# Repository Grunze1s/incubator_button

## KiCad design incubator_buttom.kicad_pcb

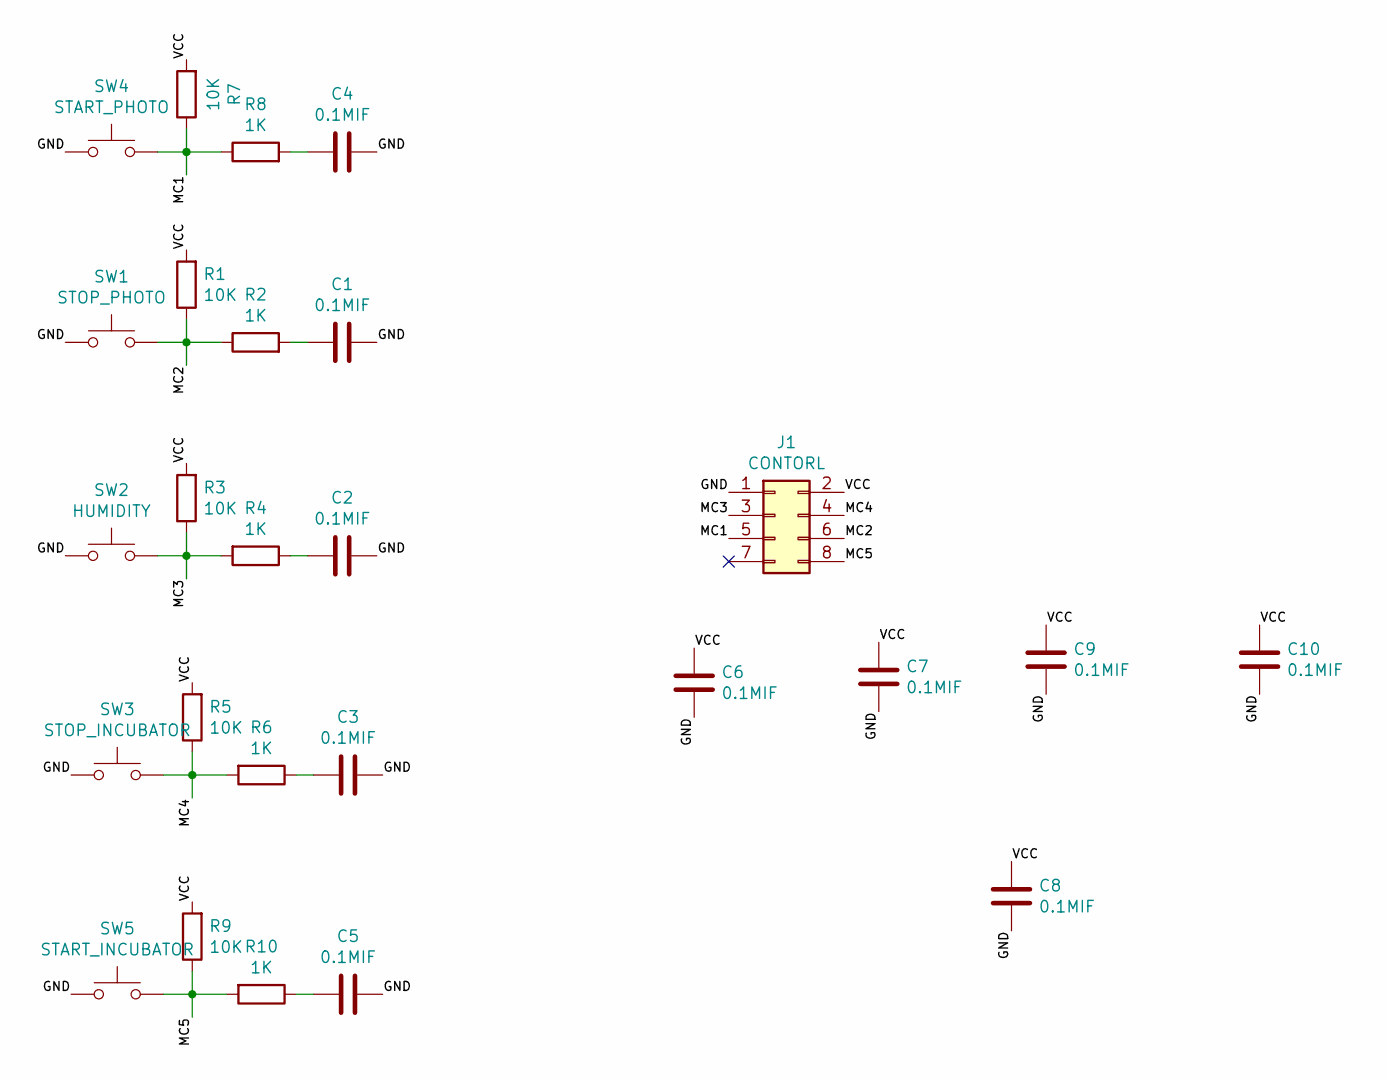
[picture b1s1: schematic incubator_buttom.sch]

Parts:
C1, C2, C3, C4, C5, C6, C7, C8, C9, C10: 0.1MIF; C_Disc_D3.0mm_W1.6mm_P2.50mm
J1: CONTORL; PinHeader_2x04_P2.54mm_Vertical
R1, R3, R5, R7, R9: 10K; R_Axial_DIN0207_L6.3mm_D2.5mm_P10.16mm_Horizontal
R2, R4, R6, R8, R10: 1K; R_Axial_DIN0207_L6.3mm_D2.5mm_P10.16mm_Horizontal
SW1: STOP_PHOTO; SW_PUSH-12mm
SW2: HUMIDITY; SW_PUSH-12mm
SW3: STOP_INCUBATOR; SW_PUSH-12mm
SW4: START_PHOTO; SW_PUSH-12mm
SW5: START_INCUBATOR; SW_PUSH-12mm

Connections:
/GND: C1.2, C2.2, C3.2, C4.1, C5.2, C6.2, C7.2, C8.2, C9.2, C10.2, J1.1, SW1.1, SW2.1, SW3.1, SW4.1, SW5.1
/MC1: J1.5, R7.1, R8.1, SW4.2
/MC2: J1.6, R1.1, R2.1, SW1.2
/MC3: J1.3, R3.1, R4.2, SW2.2
/MC4: J1.4, R5.1, R6.2, SW3.2
/MC5: J1.8, R9.1, R10.2, SW5.2
/VCC: C6.1, C7.1, C8.1, C9.1, C10.1, J1.2, R1.2, R3.2, R5.2, R7.2, R9.2
unnamed: C1.1, R2.2
unnamed: C2.1, R4.1
unnamed: C3.1, R6.1
unnamed: C4.2, R8.2
unnamed: C5.1, R10.1

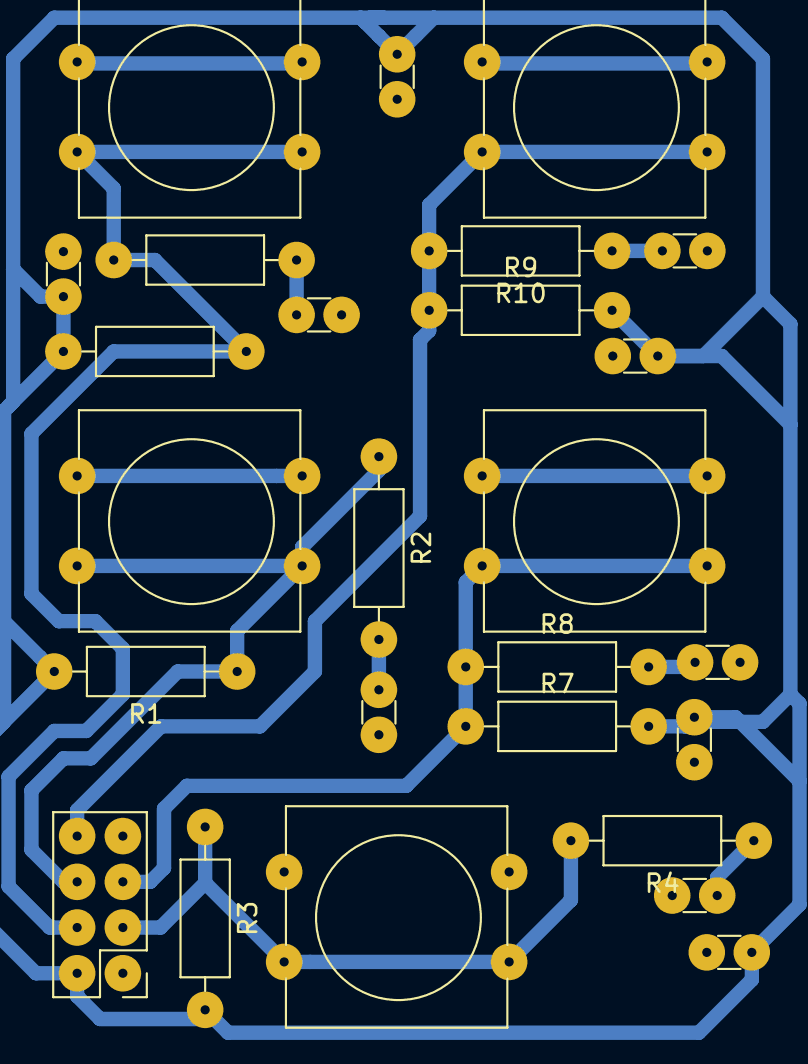
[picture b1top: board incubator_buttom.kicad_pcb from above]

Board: 2 copper layers, 26 parts (0 on the bottom side), 12 nets.

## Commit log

2019-05-24 complete
